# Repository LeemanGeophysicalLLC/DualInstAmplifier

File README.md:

# Dual Channel Instrumentation Amplifier

**THIS PRODUCT HAS BEEN RETIRED AND IS NO LONGER PRODUCED**

## Purpose

To provide an easy way to buffer, amplify, and filter analog signals. This is a
common problem in prototyping and laboratory settings where instrumentation is
often tested, changed, reconfigured, etc. This instrumentation grade product is
built around the INA128 amplifier.

## Purchasing

The dual channel instrumentation amplifier is available through Leeman
Geophysical by emailing [John R. Leeman](http://www.johnrleeman.com) at
<kd5wxb@gmail.com>.

## Project Information

This repository includes all design information, CAD files, PDF CAD output,
gerbers, etc.

Additional resources for this project include:

- [Bill of Materials](BoM.md) (BoM)
- [INA128 Datasheet](PDFs/ina128.pdf)

## License

This product is licenced under the CERN Open Hardware License 1.2. The [full
license](cern_ohl_v_1_2.txt) is included in this repository.

## Hookup Guide

Hookup is self-explanitory, but some basic guidelines and cautions
are provided below.

- Apply power and ground to the GND, Vin+, and Vin- terminals. The input voltage
should follow the specifications for the voltage regulators fitted on your
device. Normally 2-3 V over the regualted voltage is ideal.

- Apply signal to the In+ and In- terminals

- Hookup the output to your device (recorder, process, etc) via the Out+ and
Out- terminals

- Note: Regulated power is available, but be mindful of the current pulled by
sensors to not exceed the ratings of the on-board voltage regulators.

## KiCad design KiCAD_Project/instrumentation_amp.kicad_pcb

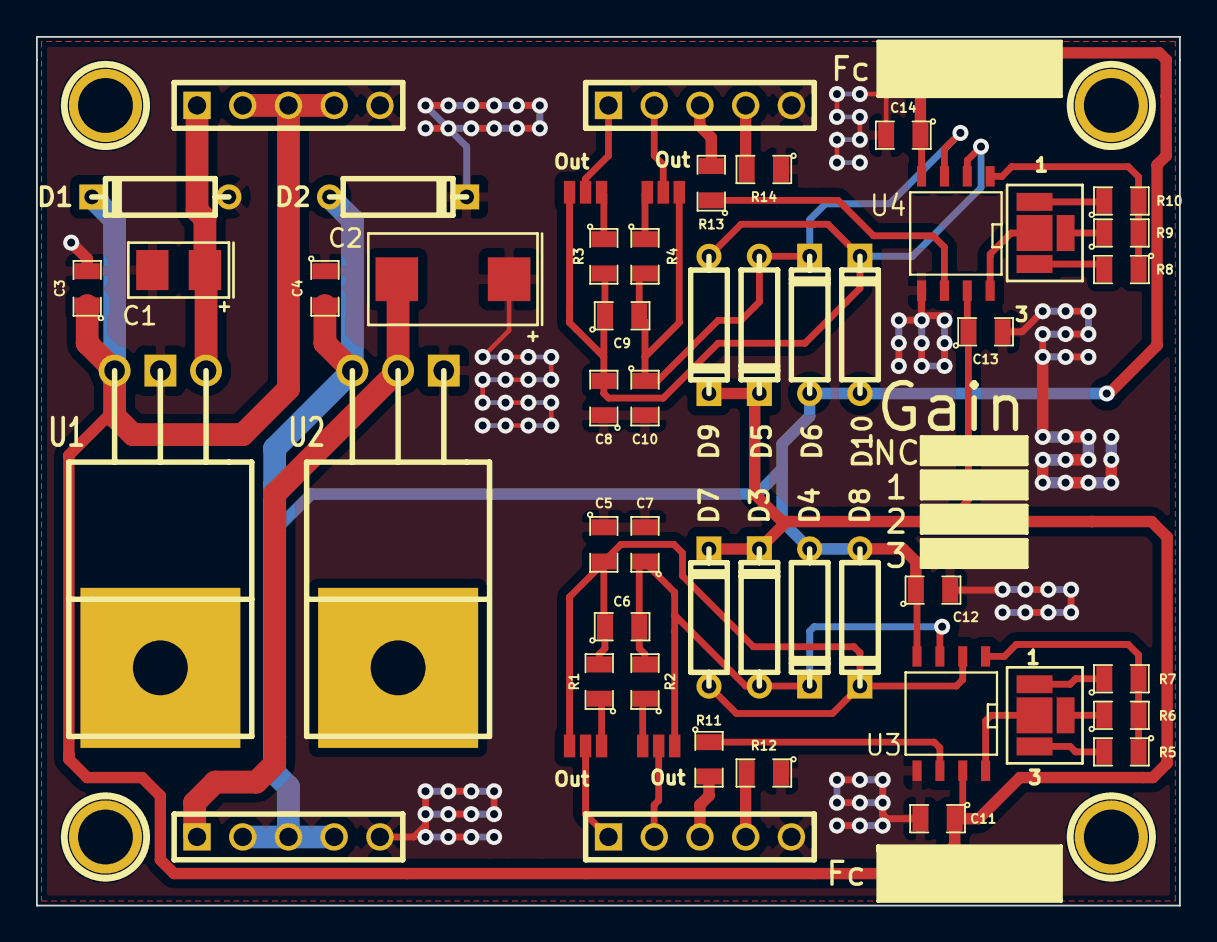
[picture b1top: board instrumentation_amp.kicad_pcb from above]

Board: 2 copper layers, 63.5 x 48.3 mm, 56 parts (0 on the bottom side), 33 nets.

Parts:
1PIN, 1PIN#2, 1PIN#3, 1PIN#4: P***; 1pin
C1: 0.33U; C1411Pol
C2: 2.2U; C2917Pol
C3, C4, C6, C9, C11, C12, C13, C14: 1U; SM0805
C5, C7, C8, C10: 0.1U; SM0805
D1, D2, D3, D4, D5, D6, D7, D8, D9, D10: 1N4001; D3
J1, J2, J3, J4: SPDT_SOLDER; SPDT
J5, J6: SP3T_SOLDER; Solder_SPTT
P1, P2, P3, P4: CONN_5; PIN_ARRAY_5x1
R1, R2, R3, R4: 154; SM0805
R5, R8: 49.9K; SM0805
R6, R9: 5.62K; SM0805
R7, R10: 511; SM0805
R11, R12, R13, R14: 0; SM0805
U1: LM7815CT; LM78XX_Numbered
U2: LM7915CT; LM79XX_Numbered
U3, U4: INA128; SO8N

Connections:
+Vin: C1.1, P1.1, U1.1
-Vin: C2.2, P2.1, U2.2
/A +IN: J2.1, P3.2
/A +OUT: P3.3, R11.2
/A -IN: J1.1, P3.1
/A -OUT: P3.4, R12.2
/B +IN: J4.1, P4.2
/B +OUT: P4.3, R13.2
/B -IN: J3.1, P4.1
/B -OUT: P4.4, R14.2
GND: C1.2, C2.1, C3.2, C4.1, C5.1, C7.2, C8.1, C10.2, C11.2, C12.2, C13.2, C14.2, D1.1, D2.2, P1.5, P2.5, P3.5, P4.5, R12.1, R14.1, U1.2, U2.1, U3.5, U4.5
unnamed: J4.2, R4.1
unnamed: J3.3, R3.1
unnamed: J6.4, R8.2
unnamed: C8.2, C9.1, D9.1, D10.2, J3.2, R3.2, U4.2
unnamed: C9.2, C10.1, D5.1, D6.2, J4.3, R4.2, U4.3
unnamed: R13.1, U4.6
unnamed: J6.2, R10.1
unnamed: J6.3, R9.1
unnamed: J6.1, U4.8
unnamed: R11.1, U3.6
unnamed: C6.2, C7.1, D3.1, D4.2, J2.3, R2.2, U3.3
unnamed: J5.1, U3.8
unnamed: C5.2, C6.1, D7.1, D8.2, J1.2, R1.2, U3.2
unnamed: R8.1, R9.2, R10.2, U4.1
unnamed: J5.3, R6.1
unnamed: J5.2, R7.1
unnamed: R5.1, R6.2, R7.2, U3.1
unnamed: J5.4, R5.2
unnamed: J1.3, R1.1
unnamed: J2.2, R2.1
VDD: C3.1, C11.1, C13.1, D1.2, D3.2, D5.2, D7.2, D9.2, P1.2, P1.3, P1.4, U1.3, U3.7, U4.7
VSS: C4.2, C12.1, C14.1, D2.1, D4.1, D6.1, D8.1, D10.1, P2.2, P2.3, P2.4, U2.3, U3.4, U4.4

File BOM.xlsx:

Quantity | P/N | Description | Price | Subtotal
1 | 399-3779-1-ND | CAP TANT 2.2UF 50V 10% 2917 | 1.9 | 1.9
1 | 399-3718-1-ND | CAP TANT 0.33UF 50V 20% 1411 | 0.55000000000000004 | 0.55000000000000004
1 | LM7815CTFS-ND | IC REG LDO 15V 1A TO220-3 | 0.7 | 0.7
1 | LM7915CTFS-ND | IC REG LDO -15V 1A TO220-3 | 0.6 | 0.6
10 | 641-1310-1-ND | DIODE GEN PURPOSE 50V 1A DO41 | 0.1 | 1
8 | P0.0ACT-ND | RES 0.0 OHM 1/8W JUMP 0805 SMD | 0.1 | 0.8
8 | 399-7409-1-ND | CAP CER 1UF 50V 10% X7R 0805 | 0.34 | 2.72
2 | INA128UA-ND | IC OPAMP INSTR 1.3MHZ 8SOIC | 8.8000000000000007 | 17.600000000000001
4 | P154DACT-ND | RES 154 OHM 1/8W .1% 0805 SMD | 0.63 | 2.52
2 | P5.62KDACT-ND | RES 5.62K OHM 1/8W .1% 0805 SMD | 0.63 | 1.26
4 | 399-1170-1-ND | CAP CER 0.1UF 50V 10% X7R 0805 | 0.1 | 0.4
1 | INSTAMP01 | PRINTED CIRCUIT BOARD | 7.94 | 7.94
2 | P511DACT-ND | RES 511 OHM 1/8W .1% 0805 SMD | 0.63 | 1.26
2 | P49.9KDACT-ND | RES 49.9K OHM 1/8W .1% 0805 SMD | 0.63 | 1.26
 |  | Total |  | 40.51

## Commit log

2014-12-07 Initial commit - Rev.A
2014-12-07 Change jumpers for better operation and rework the layout
2014-12-07 Final changes for Rev.B of PCB
2014-12-07 Add CERN OHL
2014-12-07 Improve readme and move BoM to plain text markdown
2014-12-07 Fix link in readme
2014-12-07 Fix another link in the readme
2014-12-07 Improve readme
2014-12-07 Add solder paste stencil files
2014-12-07 Update schematic PDF
2014-12-08 Fix stencil layer problem
2014-12-08 Add photos of device
2014-12-08 update photo links
2015-01-12 Add photos of Rev. B and fix README spelling.
2024-05-16 Update README.md
    THIS PRODUCT HAS BEEN RETIRED AND IS NO LONGER PRODUCED
